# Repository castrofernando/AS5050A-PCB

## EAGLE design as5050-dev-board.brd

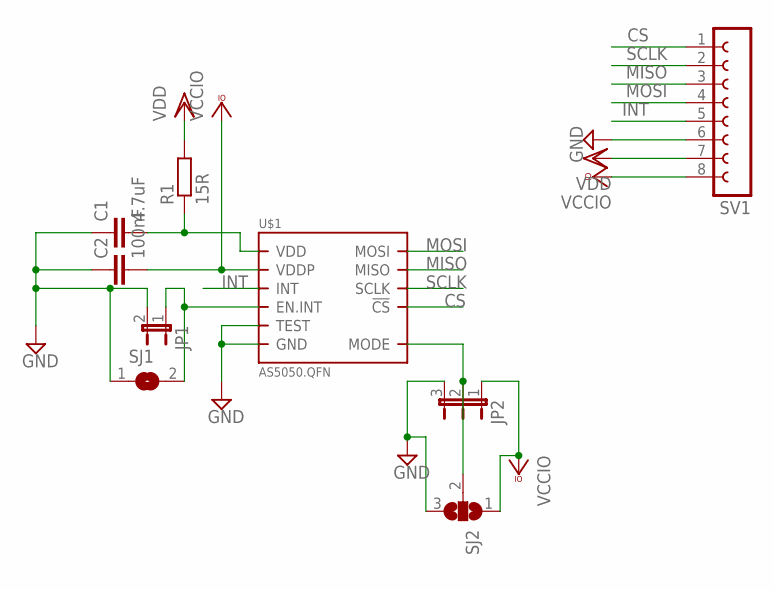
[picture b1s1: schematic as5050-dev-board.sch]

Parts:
C1: 4.7uF; C0805
C2: 100nF; C0805
JP1: JP1E; JP1
JP2: JP2E; JP2
R1: 15R; R0805
SJ1: SJ
SJ2: SJ2W; SJ_2
SV1: FE08-1; FE08
U$1: AS5050.QFN; QFN.16

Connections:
CS: SV1.1, U$1.4 (!CS)
GND: C1.1, C2.1, JP1.2, JP2.3, SJ1.1, SJ2.3, SV1.6, U$1.9 (TEST), U$1.13 (GND)
INT: SV1.5, U$1.15 (INT)
MISO: SV1.3, U$1.2 (MISO)
MOSI: SV1.4, U$1.1 (MOSI)
unnamed: JP2.2, SJ2.2, U$1.14 (MODE)
unnamed: C1.2, R1.1, U$1.12 (VDD)
unnamed: JP1.1, SJ1.2, U$1.10 (EN.INT)
SCLK: SV1.2, U$1.3 (SCLK)
VCCIO: C2.2, JP2.1, SJ2.1, SV1.8, U$1.11 (VDDP)
VDD: R1.2, SV1.7

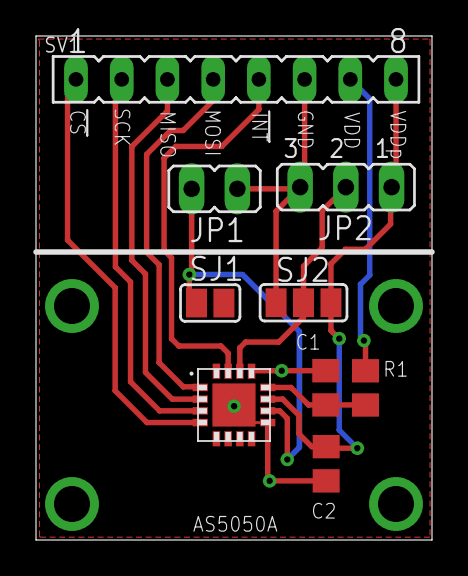
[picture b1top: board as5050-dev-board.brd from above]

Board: 2 copper layers, 22.0 x 28.0 mm, 9 parts (0 on the bottom side), 11 nets.

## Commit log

2021-08-29 placa dev finalizada - v1
